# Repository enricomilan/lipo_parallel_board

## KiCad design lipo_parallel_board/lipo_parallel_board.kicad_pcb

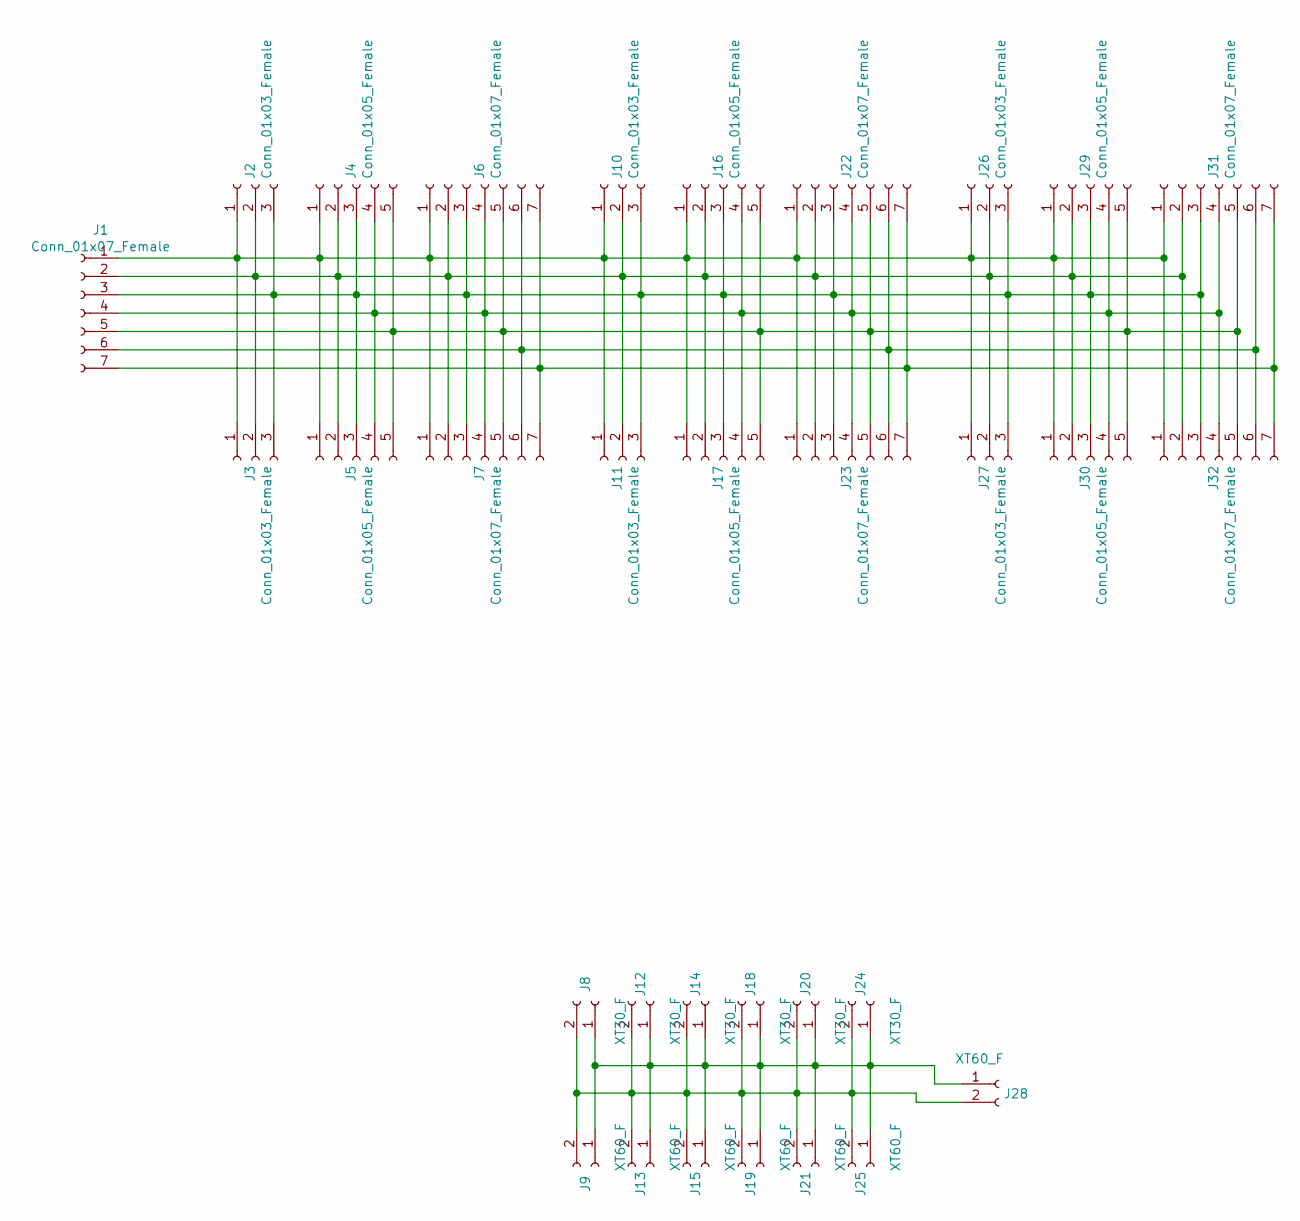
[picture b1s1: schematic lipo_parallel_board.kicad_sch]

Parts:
J1, J6, J7, J22, J23, J31, J32: Conn_01x07_Female; JST_XH_B7B-XH-AM_1x07_P2.50mm_Vertical
J2, J3, J10, J11, J26, J27: Conn_01x03_Female; JST_XH_B3B-XH-AM_1x03_P2.50mm_Vertical
J4, J5, J16, J17, J29, J30: Conn_01x05_Female; JST_XH_B5B-XH-AM_1x05_P2.50mm_Vertical
J8, J12, J14, J18, J20, J24: XT30_F; AMASS_XT30U-F_1x02_P5.0mm_Vertical
J9, J13, J15, J19, J21, J25, J28: XT60_F; AMASS_XT60-F_1x02_P7.20mm_Vertical

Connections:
unnamed: J1.1, J2.1, J3.1, J4.1, J5.1, J6.1, J7.1, J10.1, J11.1, J16.1, J17.1, J22.1, J23.1, J26.1, J27.1, J29.1, J30.1, J31.1, J32.1
unnamed: J1.2, J2.2, J3.2, J4.2, J5.2, J6.2, J7.2, J10.2, J11.2, J16.2, J17.2, J22.2, J23.2, J26.2, J27.2, J29.2, J30.2, J31.2, J32.2
unnamed: J1.3, J2.3, J3.3, J4.3, J5.3, J6.3, J7.3, J10.3, J11.3, J16.3, J17.3, J22.3, J23.3, J26.3, J27.3, J29.3, J30.3, J31.3, J32.3
unnamed: J1.4, J4.4, J5.4, J6.4, J7.4, J16.4, J17.4, J22.4, J23.4, J29.4, J30.4, J31.4, J32.4
unnamed: J1.5, J4.5, J5.5, J6.5, J7.5, J16.5, J17.5, J22.5, J23.5, J29.5, J30.5, J31.5, J32.5
unnamed: J1.6, J6.6, J7.6, J22.6, J23.6, J31.6, J32.6
unnamed: J1.7, J6.7, J7.7, J22.7, J23.7, J31.7, J32.7
unnamed: J8.1, J9.1, J12.1, J13.1, J14.1, J15.1, J18.1, J19.1, J20.1, J21.1, J24.1, J25.1, J28.1
unnamed: J8.2, J9.2, J12.2, J13.2, J14.2, J15.2, J18.2, J19.2, J20.2, J21.2, J24.2, J25.2, J28.2

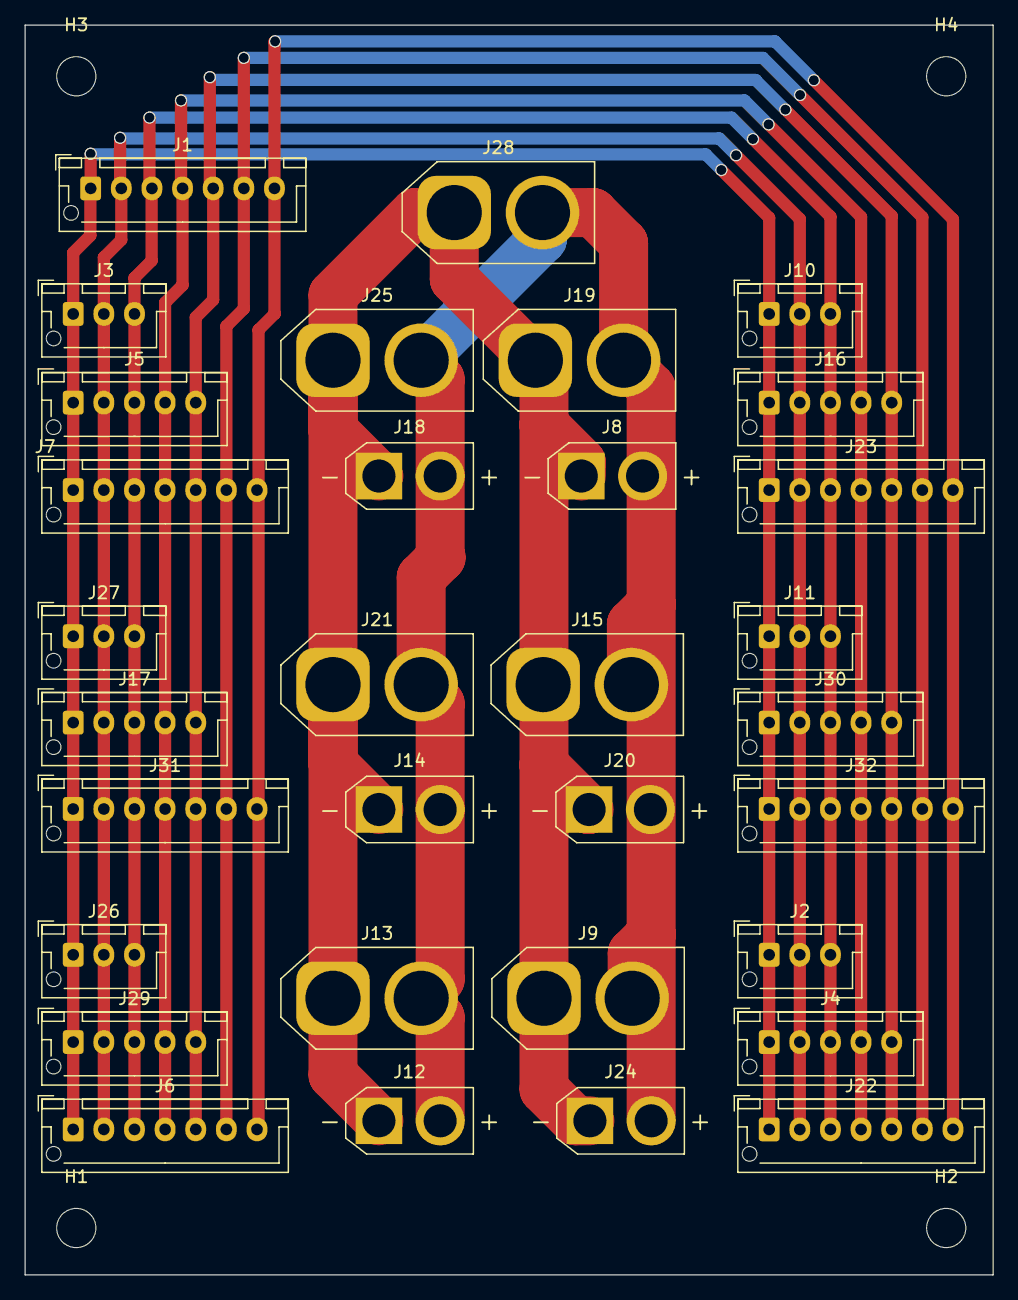
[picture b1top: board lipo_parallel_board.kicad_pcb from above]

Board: 2 copper layers, 79.0 x 102.0 mm, 36 parts (0 on the bottom side), 9 nets.

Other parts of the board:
H1, H2, H3, H4: MountingHole; MountingHole_3.2mm_M3

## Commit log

2021-06-14 iniziato lo schema e assegnati i footprint
2021-06-14 iniziato il pcb
2021-06-15 posizionato
2021-06-18 terminato il master
2021-06-18 generato file per produzione
